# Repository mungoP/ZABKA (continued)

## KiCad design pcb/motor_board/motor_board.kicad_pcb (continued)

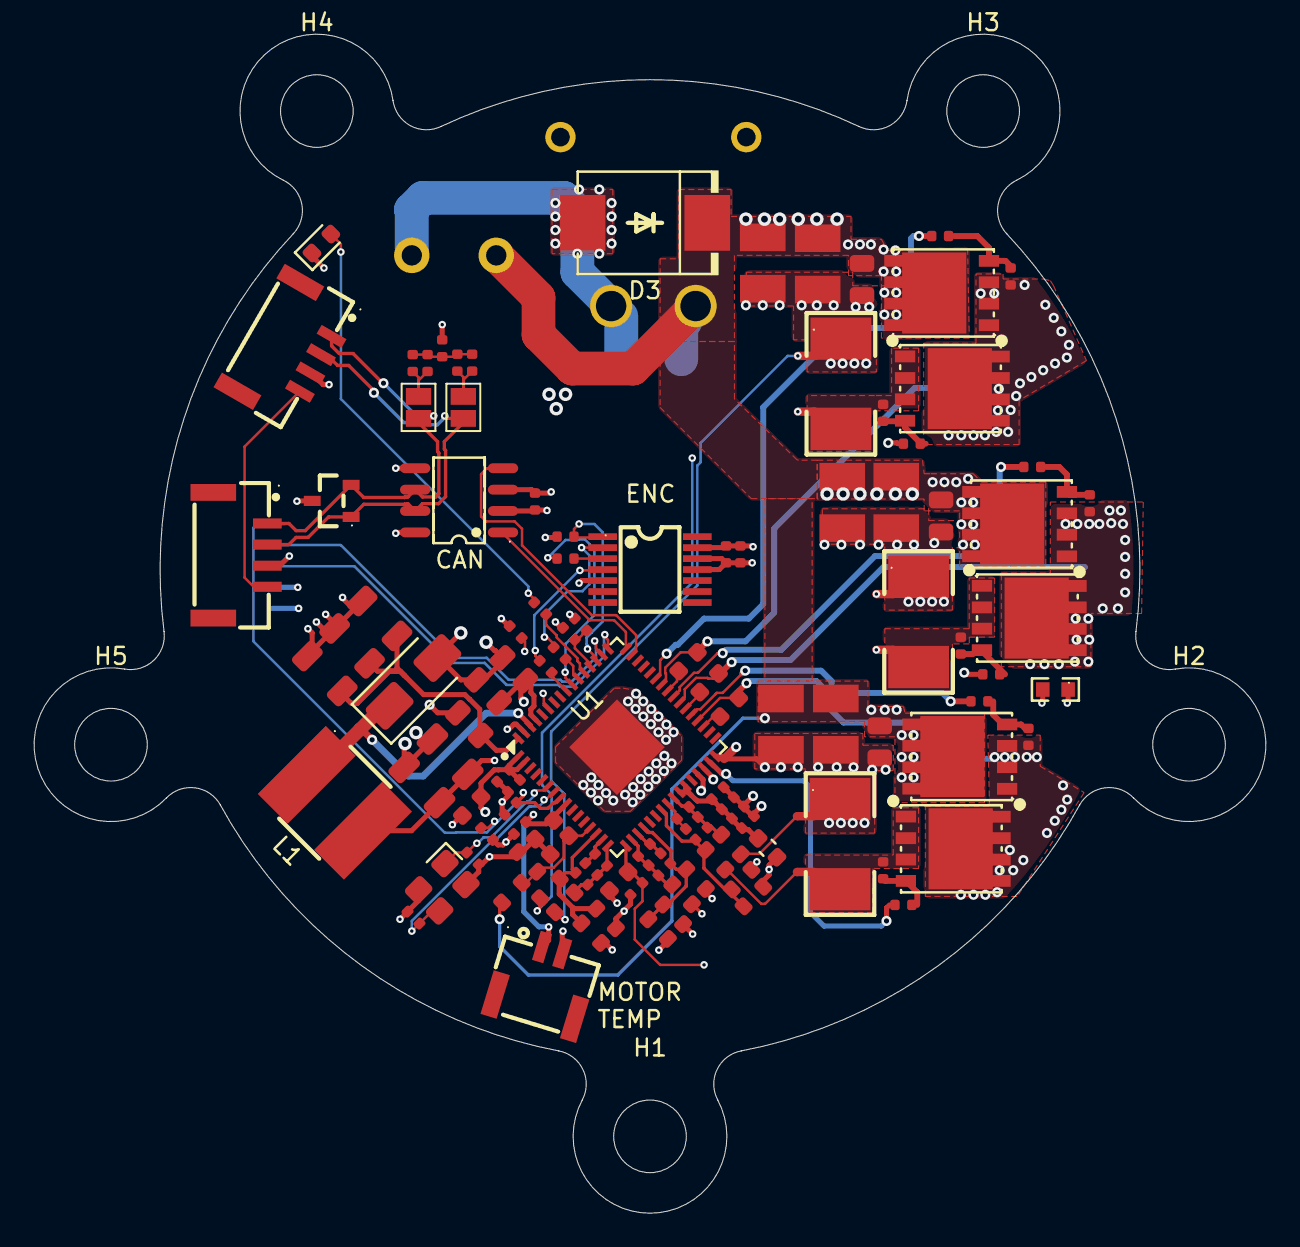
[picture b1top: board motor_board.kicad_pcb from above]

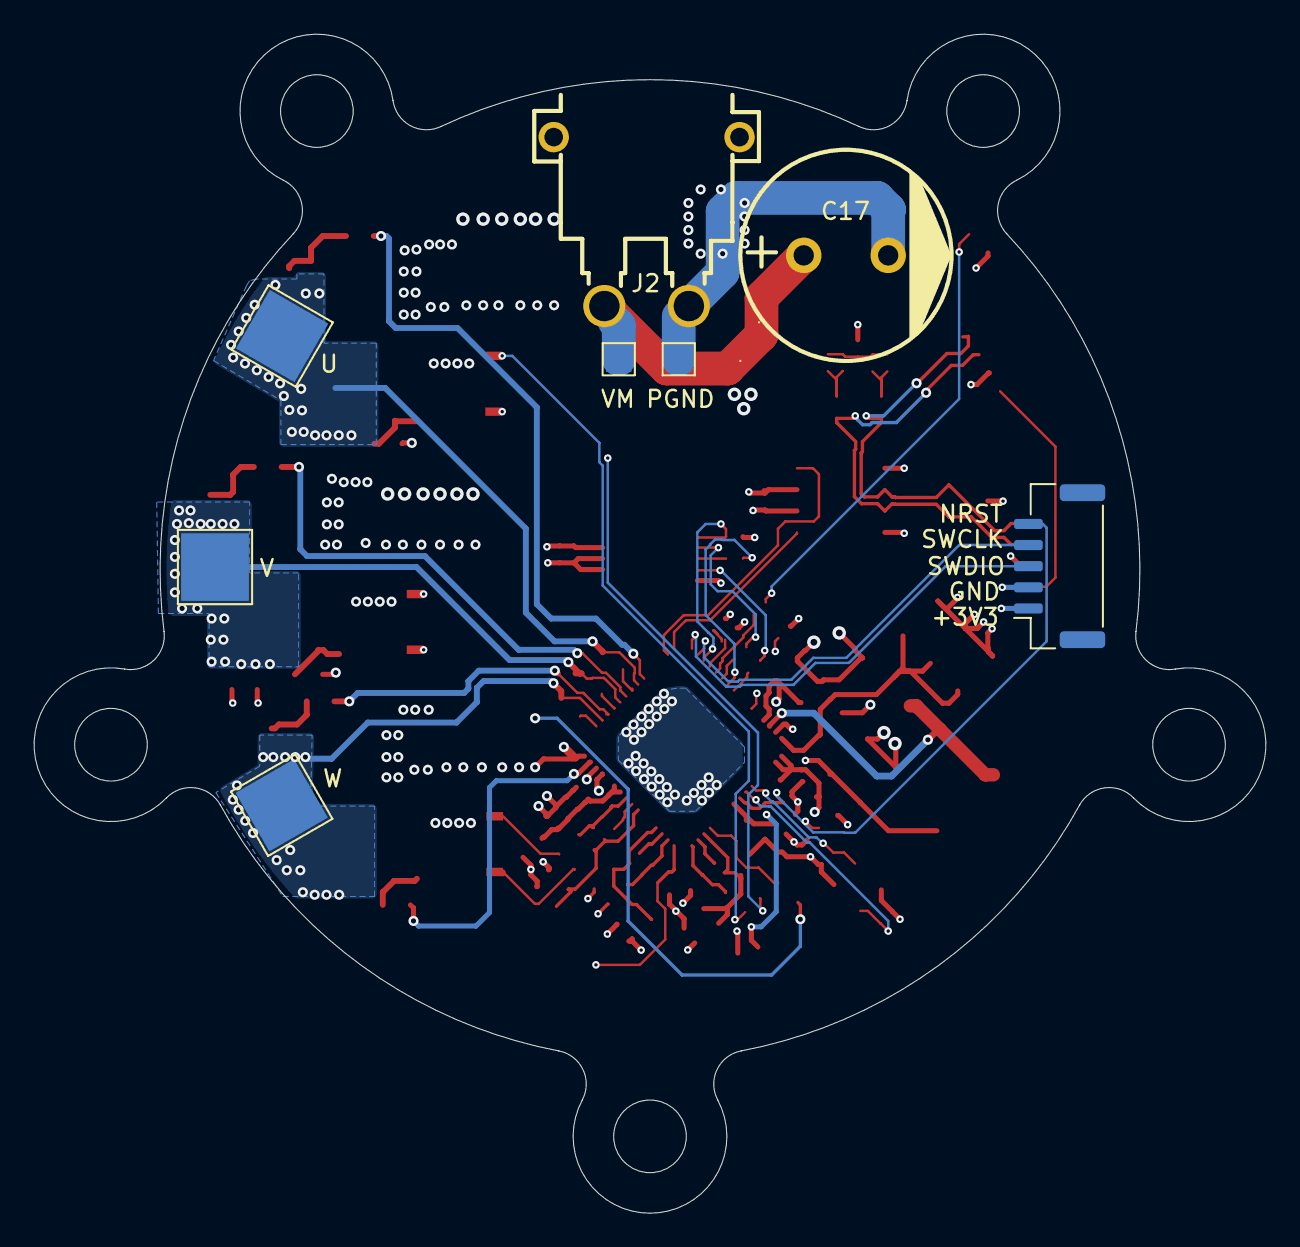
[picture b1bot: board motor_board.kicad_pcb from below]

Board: 4 copper layers, 72.9 x 69.8 mm, 132 parts (8 on the bottom side), 71 nets.

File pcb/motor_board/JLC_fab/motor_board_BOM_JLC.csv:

"Comment","Designator","Footprint","LCSC Part #"
"15pF","C1,C2","C_0402","C1548"
"100nF","C3,C4,C8,C11,C13,C21,C22","C_0402","C1525"
"10uF","C5","C_0603","C19702"
"100nF","C6,C7,C103,C203,C303","C_0805","C28233"
"22uF","C9,C10","C_1206","C12891"
"1uF","C12,C15,C23","C_0402","C52923"
"4.7uF","C14","C_0805","C1779"
"33nF","C16,C18,C19","C_0603","C21117"
"4.7nF","C20","C_0402","C1538"
"4.7uF","C101,C102,C201,C202,C301,C302","C1210_no-silk","C337978"
"1uF","C104,C204,C304","C_0603","C15849"
"10pF","C105,C205,C305","C_0402","C32949"
"100pF","C106,C206,C306","C_0402","C1546"
"Red","D1","D_0603","C2286"
"SS210","D2","D_SMA","C14996"
"5.0SMDJ51A_C2990373","D3","SMC_L6.9-W5.9-LS7.9-RD","C2990373"
"PESD1CAN,215","D4","SOT-23_L2.9-W1.3-P1.90-LS2.4-BR","C15771"
"","FB1","FB_0603","C1002"
"HC-GH-2PWT","J3","CONN-SMD_2P-P1.25_HCTL_HC-GH-2PWT","C2845397"
"SM04B-GHS-TB","J4,J5","CONN-SMD_4P-P1.25_SM04B-GHS-TB-LF-SN","C189895"
"18uH","L1","IND-SMD_L6.0-W6.0_FNR60XXS","C168016"
"HYG053N10NS1C2","Q101,Q102,Q201,Q202,Q301,Q302","PDFN-8_L5.8-W5.0-P1.27-LS6.2-BL","C2986239"
"1kΩ","R1","R_0402","C11702"
"10kΩ","R2,R9,R10,R17","R_0402","C25744"
"22kΩ","R3","R_0402","C25768"
"3.3kΩ","R4","R_0402","C25890"
"100kΩ","R5","R_0402","C25741"
"100Ω","R6,R7,R8","R_1206","C17901"
"75kΩ","R11","R_0603","C23242"
"3kΩ","R12","R_0603","C4211"
"120Ω","R13,R14,R15,R16","R_0402","C25079"
"33Ω","R18,R19,R20","R_0402","C25105"
"10Ω","R101,R103,R201,R203,R301,R303","R_0402","C25077"
"47kΩ","R102,R104,R202,R204,R302,R304","R_0402","C25792"
"100kΩ","R105,R107,R205,R207,R305,R307","R_0603","C25803"
"1.5kΩ","R106,R109,R206,R209,R306,R309","R_0603","C22843"
"1mΩ 3W 2512 shunt","R108,R208,R308","RES-SMD_L6.4-W3.2_LR2512D-3W-1MR","C500734"
"49.9kΩ","R110,R210,R310","R_0402","C25897"
"NCP18XH103F03RB","TH1","R0603","C13564"
"STSPIN32G4_C7434864","U1","VFQFPN-64_L9.0-W9.0-P0.50-TL-EP4.0","C7434864"
"TCAN3414DR","U2","SOIC-8_L4.9-W3.9-P1.27-LS6.0-BL","C22396693"
"AS5047P-ATSM","U5","TSSOP-14_L5.0-W4.4-P0.65-LS6.4-BL","C962063"
"X322525MOB4SI","X1","OSC-SMD_4P-L3.2-W2.5-BL","C9006"

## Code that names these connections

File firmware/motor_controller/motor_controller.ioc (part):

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Mcu.Name=STM32G431V(6-8-B)Tx
Mcu.Package=LQFP100
Mcu.UserName=STM32G431VBTx
PA0.Mode=IN1-Single-Ended
PA0.Signal=ADC1_IN1
PA1.Mode=Standalone
PA1.Signal=OPAMP1_VINP
PA10.GPIOParameters=GPIO_PuPd
PA10.GPIO_PuPd=GPIO_PULLDOWN
PA10.Signal=GPIO_Output
PA11.Mode=FDCAN_Activate
PA11.Signal=FDCAN1_RX
PA12.Mode=FDCAN_Activate
PA12.Signal=FDCAN1_TX
PA13.Mode=Serial_Wire
PA13.Signal=SYS_JTMS-SWDIO
PA14.Mode=Serial_Wire
PA14.Signal=SYS_JTCK-SWCLK
PA15.GPIOParameters=PinState,GPIO_PuPd
PA15.GPIO_PuPd=GPIO_PULLUP
PA15.PinState=GPIO_PIN_SET
PA15.Signal=GPIO_Output
PA2.Mode=Standalone
PA2.Signal=OPAMP1_VOUT
PA3.Mode=Standalone
PA3.Signal=OPAMP1_VINM
PA4.Mode=IN17-Single-Ended
PA4.Signal=ADC2_IN17
PA5.Mode=Standalone
PA5.Signal=OPAMP2_VINM
PA6.Mode=Standalone
PA6.Signal=OPAMP2_VOUT
PA7.Mode=Standalone
PA7.Signal=OPAMP2_VINP
PB0.Mode=Standalone
PB0.Signal=OPAMP3_VINP
PB1.Mode=Standalone
PB1.Signal=OPAMP3_VOUT
PB2.Mode=Standalone
PB2.Signal=OPAMP3_VINM
PB3.Mode=Full_Duplex_Master
PB3.Signal=SPI3_SCK
PB4.Mode=Full_Duplex_Master
PB4.Signal=SPI3_MISO
PB5.Mode=Full_Duplex_Master
PB5.Signal=SPI3_MOSI
PC0.Mode=IN6-Single-Ended
PC0.Signal=ADC1_IN6
PC8.Mode=I2C
PC8.Signal=I2C3_SCL
PC9.Mode=I2C
PC9.Signal=I2C3_SDA
PD2.Signal=GPIO_Output
PE10.Mode=PWM Generation2 CH2 CH2N
PE10.Signal=TIM1_CH2N
PE11.Signal=S_TIM1_CH2
PE12.Mode=PWM Generation3 CH3 CH3N
PE12.Signal=TIM1_CH3N
PE13.Signal=S_TIM1_CH3
PE14.Signal=GPIO_Input
PE15.GPIOParameters=GPIO_PuPd
PE15.GPIO_PuPd=GPIO_PULLUP
PE15.Mode=Activate-Break-Input
PE15.Signal=TIM1_BKIN
PE7.GPIOParameters=GPIO_PuPd
PE7.GPIO_PuPd=GPIO_PULLDOWN
PE7.Signal=GPIO_Output
PE8.Mode=PWM Generation1 CH1 CH1N
PE8.Signal=TIM1_CH1N
PE9.Signal=S_TIM1_CH1
PF0-OSC_IN.Mode=HSE-External-Oscillator
PF0-OSC_IN.Signal=RCC_OSC_IN
PF1-OSC_OUT.Mode=HSE-External-Oscillator
PF1-OSC_OUT.Signal=RCC_OSC_OUT
RCC.HSE_VALUE=25000000
RCC.SYSCLKFreq_VALUE=170000000
RCC.SYSCLKSource=RCC_SYSCLKSOURCE_PLLCLK
board=custom
